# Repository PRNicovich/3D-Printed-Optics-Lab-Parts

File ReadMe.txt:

This repo holds a number of parts created for an optical/fluorescence microscopy lab.  These parts don't warrant a repo of their own, but some or all may be useful for others doing similar work.  

Happy to send source CAD files of any that may be desired.  If you do come up with similar or derivative parts of your own it'd be great to have them included in this repo, either in your own fork or adding as a contributor.

Prices are given as of January 2017 through Shapeways. These are meant to be guidelines for the cost of a part and do not indicate that these parts are for sale directly through this repository.

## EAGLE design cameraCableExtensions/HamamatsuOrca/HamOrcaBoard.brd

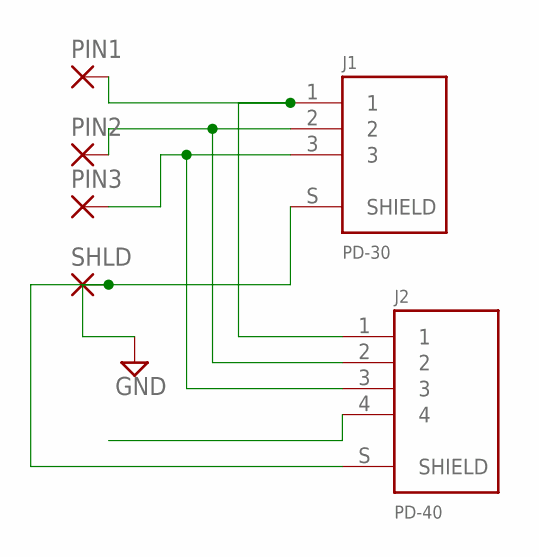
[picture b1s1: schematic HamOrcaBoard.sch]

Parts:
J1: PD-30; CUI_PD-30
J2: PD-40; CUI_PD-40
PIN1, PIN2, PIN3: 3,81/1,4
SHLD: 3,81/1,4

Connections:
GND: J1.S (SHIELD), J2.S (SHIELD), SHLD.1
unnamed: J1.1, J2.1, PIN1.1
unnamed: J1.2, J2.2, PIN2.1
unnamed: J1.3, J2.3, PIN3.1

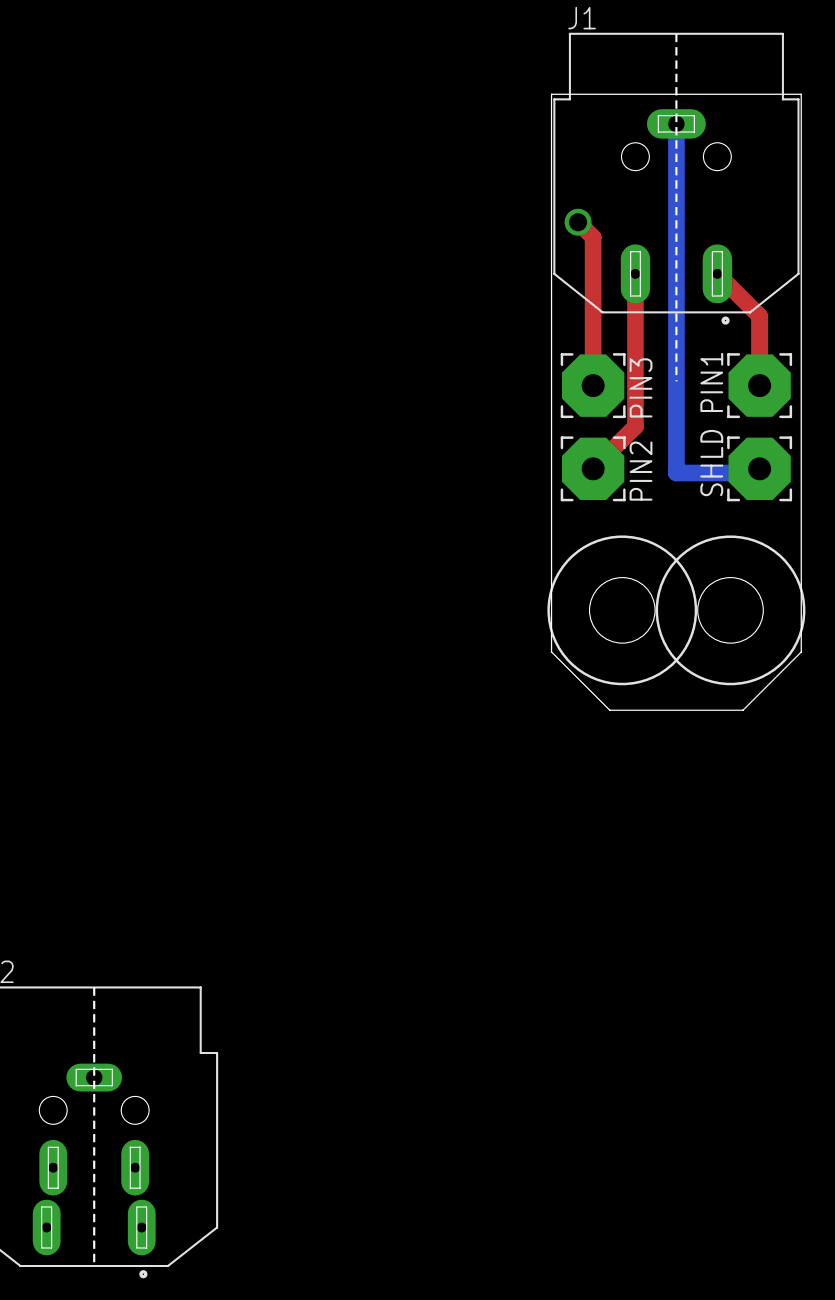
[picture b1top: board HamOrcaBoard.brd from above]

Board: 2 copper layers, 46.3 x 75.2 mm, 8 parts (0 on the bottom side), 4 nets.

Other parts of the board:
U$1, U$2: DRIL-4

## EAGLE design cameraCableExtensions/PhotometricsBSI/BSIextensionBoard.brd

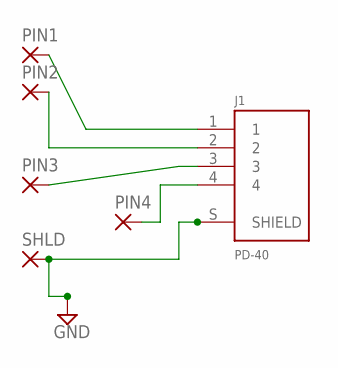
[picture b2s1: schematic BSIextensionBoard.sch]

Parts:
J1: PD-40; CUI_PD-40
PIN1, PIN2, PIN3, PIN4: 3,81/1,4
SHLD: 3,81/1,4

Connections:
GND: J1.S (SHIELD), SHLD.1
unnamed: J1.1, PIN1.1
unnamed: J1.2, PIN2.1
unnamed: J1.3, PIN3.1
unnamed: J1.4, PIN4.1

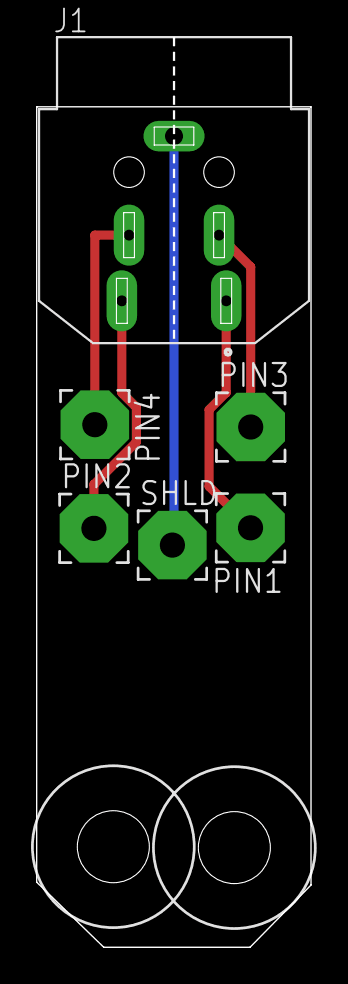
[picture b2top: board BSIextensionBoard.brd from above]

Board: 2 copper layers, 15.2 x 50.5 mm, 8 parts (0 on the bottom side), 5 nets.

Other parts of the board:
U$1, U$2: DRIL-4

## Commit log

2016-06-14 Initial commit of repo.
2016-06-20 Uploaded correct version for ArduinoTableMount.stl
2016-06-21 Added Thorlabs XE25DG adapter part to repo.
2016-06-26 Added half-inch filter holder for Vortran lasers.
2016-06-26 Updated Half-inch filter block description file.
2016-09-08 Added folder for coolant tube optics mounts.
2016-09-08 Clarified readme on imperial threads, compatability.
2016-09-19 Added magnet coolant tube mount.
2016-10-12 Added LLS table tray files.
2017-01-16 Added pricing info for parts.
2017-01-17 Added Arduino mount for laser heat sink block spot.
2017-01-17 Added files to print 16 clips per file.
2017-10-18 Added ASI Large Volume Chamber files.
2017-10-18 Updated ASI Large Volume Stage readme file.
2017-10-26 Added files for ceramic coverslip holder.
2019-07-22 Added \cameraCableExtensions\ folder and contents.
2019-07-22 Removed raw image file of soldered board.
